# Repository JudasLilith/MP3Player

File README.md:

.png)

__Yet another MP3 Player, based on the DFRobot player. made for Hack Club Fallout(woohoo!!)__

## Introduction

Last year, the state of texas passed a law banning phones in all public schools. This came as a devastating effect for people who used their phones for academic purposes and people who listened to music in their free time. This situation made me find ways to listen to my playlist, and prompted me to make this project.

This project is highly influenced from other similar projects, such as:

* <https://github.com/Neutrino-1/Arduino-Soundpod> (this one even has a [instructables page](https://www.instructables.com/Arduino-Retro-Style-MP3-Player/))
* <https://fallout.hackclub.com/projects/755>
* <https://fallout.hackclub.com/projects/2789>

The MP3Player works by using the DFrobot DFPlayer, where all the songs are stored inside a microSD card. Each of the files have a specific 4-digit number, and those are used to find or traverse through the music.

## Gallery

### The BOM (Bill of Materials)

| __Name__ | __Link__ | __info__ |
| --- | :----: | :----: |
|DFRobot MP3 Player module | [original seller](https://www.dfrobot.com/product-1121.html) |lwk, clones do not matter just get cheap clones from Aliexpressor or sumn
| SD card | [amazon link](https://www.amazon.com/SanDisk-2-Pack-microSDHC-Memory-2x32GB/dp/B08J4HJ98L?dib=eyJ2IjoiMSJ9.vZOPhvVy61i3F4YWb85gvBN9TivlWRxkBdxGT6mhkzrr2qoTEqy-T085dcQkiHgQ50T8wFaHobhX3Bn9akFQ2pMYzg3VztGHldnhl0s0_EYRB-Rp3KkVSxzjlvpcTmK7J2RY-2pRxAW9iRSYLtOTnUO-DiF9LnDR1HmU_nCGZO2OBTu7ECz8RS16p9LKuOA_9fKiMNsyfdiDCwbHfyx_5KB52vt29O6nbrIOiH5t2c0.TdA2tApy7VmIYyeuANhf7nGBc2UW4OnBapWOyu5gnOk&dib_tag=se&keywords=sandisk+sd+cards&qid=1779154655&sr=8-1) | any type of SD card will do, this was what I was just used. |
| custom PCB board | [inside the step file](/link) | Will add the files in a minute |
|SSD1036 | [amazon link for bulk](https://www.amazon.com/Hosyond-Display-Self-Luminous-Compatible-Raspberry/dp/B09T6SJBV5?dib=eyJ2IjoiMSJ9.6uJuI5cggaMKzcvI3mu-dvbLKlj0wOWwlcQl8xbyRfobJ3b6c3TsCgL8d5_2lj8bLpLwA4m1hgeH44EIKLIRiKn3pWcYvAocKu5288WeMdbQmOFhvJb4ijzHVK9Dped37QJYRIt5XDpLywYeOpeQUfzYAYDSUoPxFf_L-H85uGiz8-c98xMIucxSm6GAxhSut_ObX1kKdCcg77o59dNTfLinpqeD7YGn54MTBzKJl70.jMLZNSco5vdolf4Xf3qk7ZSXTGG4EDmd4ni-0WYy83k&dib_tag=se&keywords=SSD1306&qid=1779242639&sr=8-3) | Anything is fine, just make sure it's compatible with the Adafruit display library |
|4 Buttons (depending on what kind of keys you want, alter the kicad pcb file) | N/A | I personally just use the common button keys on almost every arduino kits |
|6 M2 nuts | [amazon link](https://www.amazon.com/Fgruh-M2-M3-M4-M5/dp/B0FGX9JGC5?crid=2NT24WAXE91QV&dib=eyJ2IjoiMSJ9.bTnvM_SQYLnYjyxSTAjjl1uodreFeuz-DqdsShjjYoTxPRmYdLp0gsPrWAr6kup0ESoJtdRbpmtmB9dMdnlQeEkzhxx_JS9wCRuVgj6k9fjj47v8lrjGXZ4dK8EqRT23Y3vk3vRO8XoYZ6VclKd2-avzBNO6XllpkOqiz-HR-MxHtlevnvKI35uXiU8fplah3sifPqZ165s9ZiDBFIUkXdSgNPQKdu1qo5lP5ZVZgW8.DFK3ayGbvIMHyTdY6YLHADBtloOBhNXhUbNScAJskyk&dib_tag=se&keywords=m2%2Bbolt%2Bsocket%2Bhead%2Bassortment&qid=1781308895&sprefix=m2%2Bbolt%2Bscket%2Bhead%2Bassortment%2Caps%2C143&sr=8-5&th=1) | Any M2 nuts and bolts will do, just make sure that the nuts are at least 4.5mm on each parallel side.
| 3 M2-5mm Bolts | use above link | For the bottom plate of the casing |
| 3 M2-15mm Bolts | use above link | For connecting the middle casing, along with the top casing. |
| 1 18650 Cell   | [amazon link](https://www.amazon.com/Flat-Top-Universal-Flashlights-Headlamps/dp/B0FQB9BGTP?crid=1RIBPPK5YQ2XI&dib=eyJ2IjoiMSJ9.la5kUCHeIe5Hy9lp-aRFXf1biT_IP1jnohu_-zaT70c0UjlWM6PZzRdu6msWVry0Oje2jAw_JYBpu8xreDR2Mpf4bH8TR8p9vrkxXQaNZVcaHYTlueuKfAtJaiygecx0lI4VajVgjj3YgMi6hLi0eos32sLm04mkFIki4WSkoZhJA02npbFF9scdcbxaeMZ7Ru5O2Tp95RaYEZvwElCxKiYuUUnIPMQZ8hEXlhlNs18.HKAvgbk3hOwBcOJNn1SDUT5FWvKfBPtH43WR3UvdbLs&dib_tag=se&keywords=18650&qid=1781460401&sprefix=18650%2Caps%2C176&sr=8-4&th=1) | they normally sell in bulk, there probably are better ways for you to source these parts.|

### Warning

__Depending on the pack, make sure that you have a method to cut out the leeway remain of the bolts.__

### Custom music

  You can add Custom music to your file, just inside the ./firmware/Music&Script/ for a python file, that would let you import the list yourself and then number them on your own.
  Make sure that the files are in place for the python scripts, and then run the scripts. The script name is "updater.py"

Further information about the [DFRobot Module can be found here.](https://wiki.dfrobot.com/dfr0299/)

## Assembly

* First, make a gerber file with the KiCad files and solder each one in this order:

* The DFPlayer-

* The Battery Holder -

* Arduino Nano-

* The Screen-

* The Buttons

Be sure to print the casing, and have some way to tighten nuts and bolts.

CAD file Link: <https://cad.onshape.com/documents/ecd8843b791ff5437d08f02d/w/4fa01a5ba4f86aa9473803eb/e/f34659960ea4cbceb5ca3625>

## Using the player

* in flashing the code, do as you will with any microcontroller by connecting to the Arduino IDE, maintain a connection, and press flash.

* Press the up button to toggle stop and play.

* The Right Button passes through each music, and the Left button goes to the previous music

* The Up + Right button to increase volume, the Down + Left button to decrease it.

## Have fun making

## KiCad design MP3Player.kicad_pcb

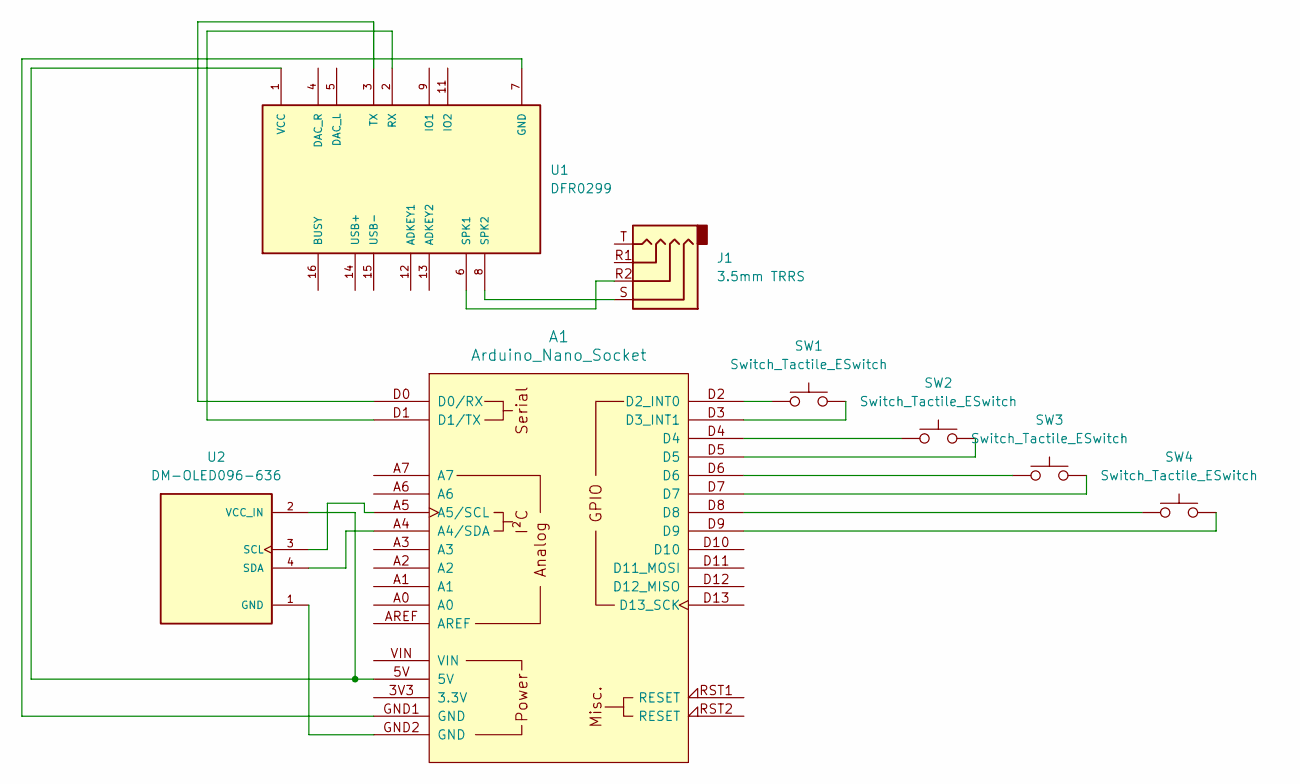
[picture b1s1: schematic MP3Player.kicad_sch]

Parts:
A1: Arduino_Nano_Socket
J1: 3.5mm TRRS; Audio_Jack_3.5mm_TRRS_SMD_RA
SW1, SW2, SW3, SW4: Switch_Tactile_ESwitch; Button_ESwitch_TL3315NF100Q_4.5x4.5mm
U1: DFR0299; MODULE_DFR0299
U2: DM-OLED096-636; MODULE_DM-OLED096-636; PARTREV 2018-09-10

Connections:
GND: A1.GND1 (GND), U1.7 (GND), U1.10 (GND)
unnamed: A1.A4 (A4/SDA), U2.4 (SDA)
unnamed: A1.A5 (A5/SCL), U2.3 (SCL)
unnamed: A1.D0 (D0/RX), U1.3 (TX)
unnamed: A1.D1 (D1/TX), U1.2 (RX)
unnamed: A1.D2 (D2_INT0), SW1.1, SW1.2
unnamed: A1.D3 (D3_INT1), SW1.3, SW1.4
unnamed: A1.D4, SW2.1, SW2.2
unnamed: A1.D5, SW2.3, SW2.4
unnamed: A1.D6, SW3.1, SW3.2
unnamed: A1.D7, SW3.3, SW3.4
unnamed: A1.D8, SW4.1, SW4.2
unnamed: A1.D9, SW4.3, SW4.4
unnamed: J1.R2, U1.6 (SPK1)
unnamed: J1.S, U1.8 (SPK2)
unnamed: A1.5V, U1.1 (VCC), U2.2 (VCC_IN)
unnamed: A1.GND2 (GND), U2.1 (GND)

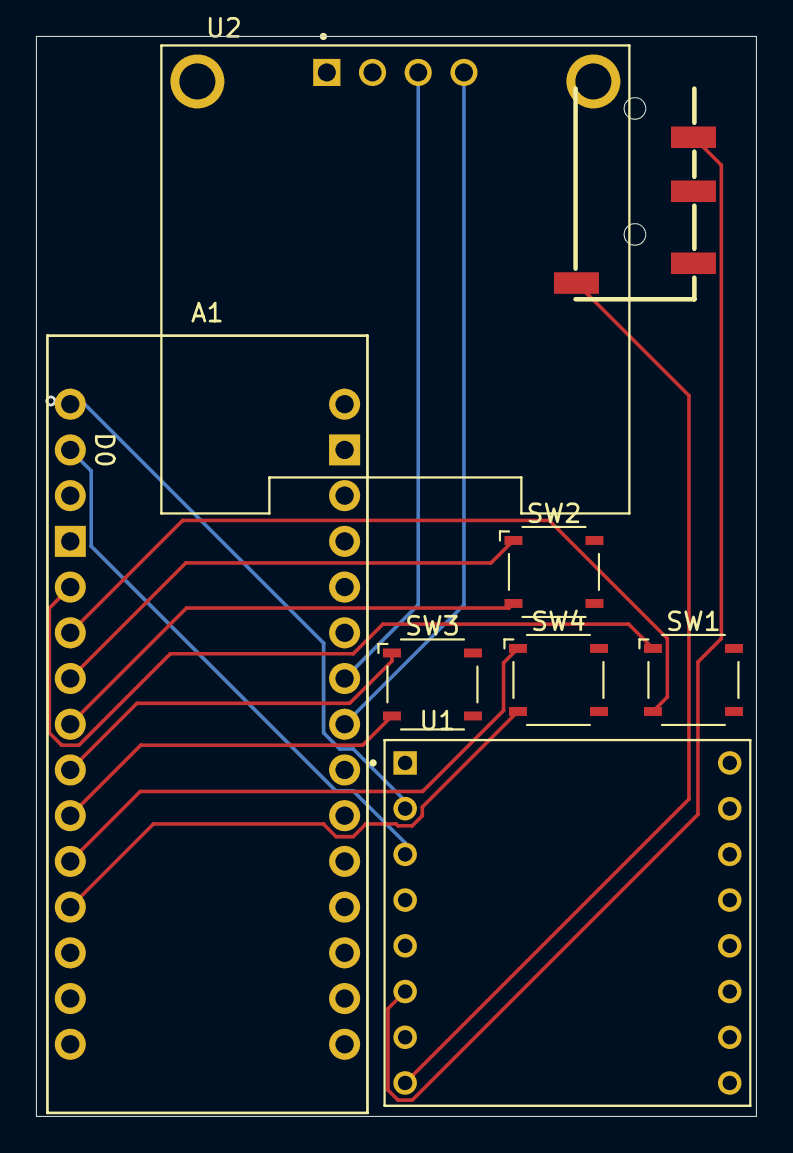
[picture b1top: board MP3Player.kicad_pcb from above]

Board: 4 copper layers, 40.0 x 60.0 mm, 8 parts (0 on the bottom side), 17 nets.

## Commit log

2026-05-16 added platformio
2026-05-16 now its probably solved
2026-05-18 new push for working on programming
2026-05-19 worked on readme
2026-05-21 Just finished the buttons working, time to grind on lopaka
2026-05-22 worked on other screens and now adding batteries
2026-06-01 general update
2026-06-03 made some logos
    logos
2026-06-13 added images
2026-06-14 finished readme
2026-06-15 uploading program
2026-06-15 upload step files
2026-06-15 final push
2026-06-16 reorganizing
2026-06-16 reorganizing v2
2026-06-19 altered zine
2026-06-20 first commit, adding new lines of code
